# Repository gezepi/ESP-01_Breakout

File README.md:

# ESP-01_Breakout
A simple breakout board for an ESP-01 that has a protoboard area.  Provides 5v and 3v3 rails.

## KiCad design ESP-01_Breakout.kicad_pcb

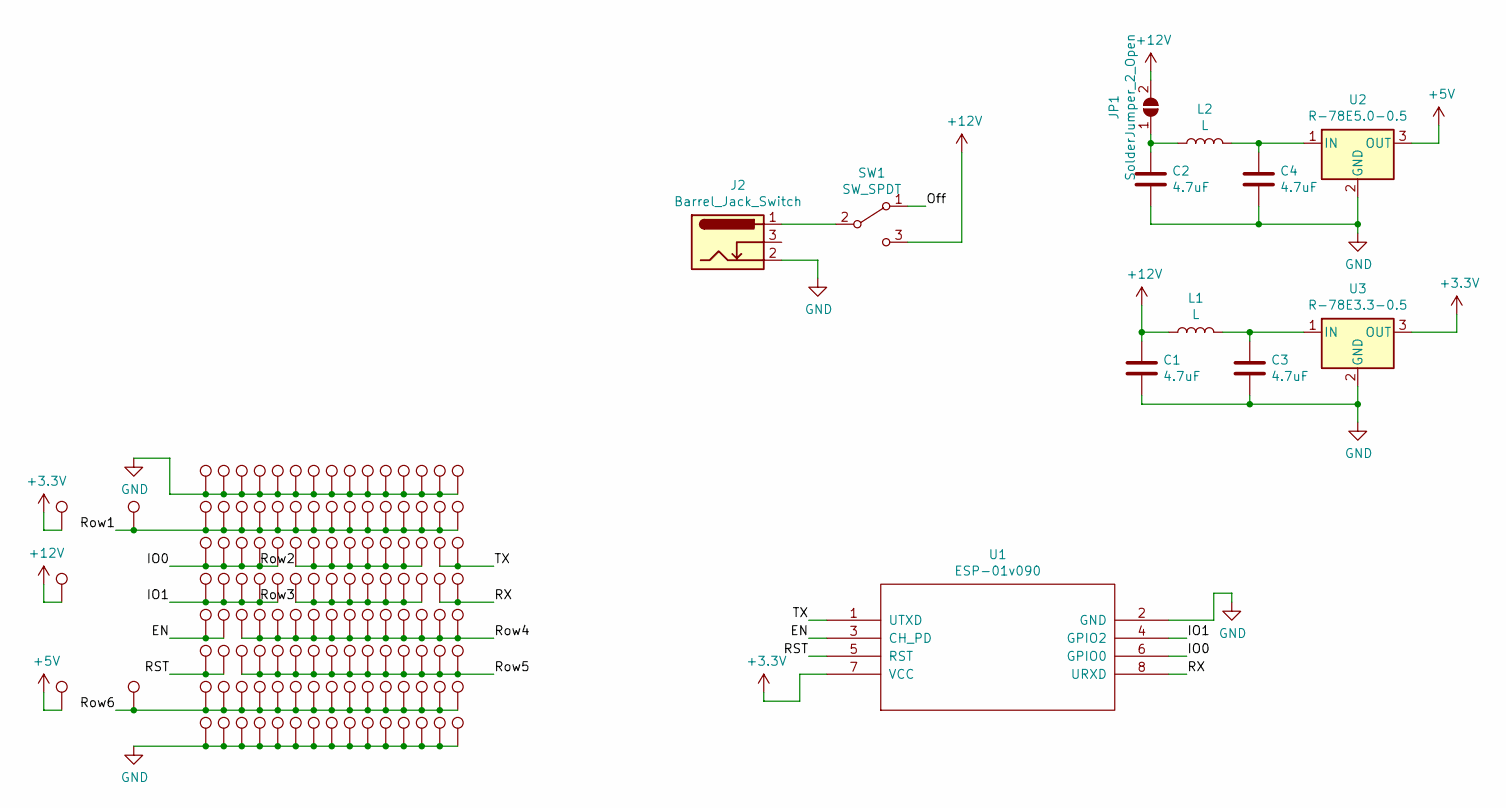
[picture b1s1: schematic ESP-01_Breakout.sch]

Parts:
C1, C2, C3, C4: 4.7uF; C_0805_2012Metric_Pad1.15x1.40mm_HandSolder; DigikeyPN 490-10751-1-ND
J2: Barrel_Jack_Switch; BarrelJack_Horizontal; DigikeyPN 2073-DCJ235-05-A-K1-K-ND
JP1: SolderJumper_2_Open; SolderJumper-2_P1.3mm_Open_TrianglePad1.0x1.5mm
L1, L2: L; IND_RLS-397; DigikeyPN 945-30004967-ND
SW1: SW_SPDT; SS312SAH4-R; DigikeyPN 360-2924-1-ND
TP1, TP2, TP3, TP4, TP5, TP6, TP7, TP8, TP9, TP10, TP11, TP12, TP13, TP14, TP15, TP16, TP17, TP18, TP19, TP20, TP21, TP22, TP23, TP24, TP25, TP26, TP27, TP28, TP29, TP30, TP31, TP32, TP33, TP34, TP35, TP36, TP37, TP38, TP39, TP40, TP41, TP42, TP43, TP44, TP45, TP46, TP47, TP48, TP49, TP50, TP51, TP52, TP53, TP54, TP55, TP56, TP57, TP58, TP59, TP60, TP61, TP62, TP63, TP64, TP65, TP66, TP67, TP68, TP69, TP70, TP71, TP72, TP73, TP74, TP75, TP76, TP77, TP78, TP79, TP80, TP81, TP82, TP83, TP84, TP85, TP86, TP87, TP88, TP89, TP90, TP91, TP92, TP93, TP94, TP95, TP96, TP97, TP98, TP99, TP100, TP101, TP102, TP103, TP104, TP105, TP106, TP107, TP108, TP109, TP110, TP111, TP112, TP113, TP114, TP115, TP116, TP117, TP118, TP119, TP120, TP121, TP122, TP123, TP124, TP125: TestPoint; TP
U1: ESP-01v090; ESP-01; DigikeyPN SAM1212-04-ND
U2: R-78E5.0-0.5; Converter_DCDC_RECOM_R-78E-0.5_THT; DigikeyPN 945-1648-5-ND
U3: R-78E3.3-0.5; Converter_DCDC_RECOM_R-78E-0.5_THT; DigikeyPN 945-1661-5-ND

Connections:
+3V3: TP121.1, U1.7 (VCC), U3.3 (OUT)
+5V: TP122.1, U2.3 (OUT)
+12V: C1.1, JP1.2 (B), L1.1, SW1.3 (C), TP125.1
/EN: TP109.1, TP117.1, U1.3 (CH_PD)
/IO0: TP3.1, TP11.1, TP19.1, TP27.1, TP35.1, U1.6 (GPIO0)
/IO1: TP4.1, TP12.1, TP20.1, TP28.1, TP36.1, U1.4 (GPIO2)
/Off: SW1.1 (A)
/RST: TP110.1, TP118.1, U1.5 (RST)
/RX: TP108.1, TP116.1, U1.8 (URXD)
/Row1: TP2.1, TP10.1, TP18.1, TP26.1, TP34.1, TP42.1, TP50.1, TP58.1, TP66.1, TP74.1, TP82.1, TP90.1, TP98.1, TP106.1, TP114.1, TP123.1
/Row2: TP43.1, TP51.1, TP59.1, TP67.1, TP75.1, TP83.1, TP91.1, TP99.1
/Row3: TP44.1, TP52.1, TP60.1, TP68.1, TP76.1, TP84.1, TP92.1, TP100.1
/Row4: TP5.1, TP13.1, TP21.1, TP29.1, TP37.1, TP45.1, TP53.1, TP61.1, TP69.1, TP77.1, TP85.1, TP93.1, TP101.1
/Row5: TP6.1, TP14.1, TP22.1, TP30.1, TP38.1, TP46.1, TP54.1, TP62.1, TP70.1, TP78.1, TP86.1, TP94.1, TP102.1
/Row6: TP7.1, TP15.1, TP23.1, TP31.1, TP39.1, TP47.1, TP55.1, TP63.1, TP71.1, TP79.1, TP87.1, TP95.1, TP103.1, TP111.1, TP119.1, TP124.1
/TX: TP107.1, TP115.1, U1.1 (UTXD)
GND: C1.2, C2.2, C3.2, C4.2, J2.2, TP1.1, TP8.1, TP9.1, TP16.1, TP17.1, TP24.1, TP25.1, TP32.1, TP33.1, TP40.1, TP41.1, TP48.1, TP49.1, TP56.1, TP57.1, TP64.1, TP65.1, TP72.1, TP73.1, TP80.1, TP81.1, TP88.1, TP89.1, TP96.1, TP97.1, TP104.1, TP105.1, TP112.1, TP113.1, TP120.1, U1.2 (GND), U2.2 (GND), U3.2 (GND)
unnamed: C2.1, JP1.1 (A), L2.1
unnamed: C3.1, L1.2, U3.1 (IN)
unnamed: C4.1, L2.2, U2.1 (IN)
unnamed: J2.1, SW1.2 (B)

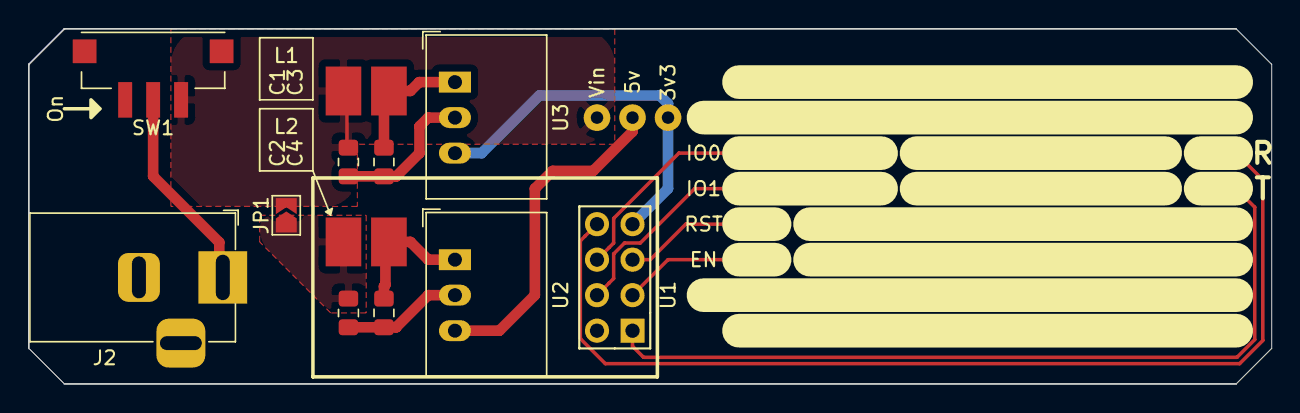
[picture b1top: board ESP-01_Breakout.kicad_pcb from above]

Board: 2 copper layers, 88.9 x 25.4 mm, 137 parts (0 on the bottom side), 20 nets.

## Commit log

2020-02-21 Initial Commit
    Has terminal block as power input
2020-02-21 Barrel Jack, Smaller Switch
2020-02-21 BOM, gitignore Update
2020-02-21 Add Release Action
    See here: https://github.com/actions/create-release
2020-02-21 Revert "Add Release Action"
    This reverts commit 27405666da6dad12f90c6b98284779e225da4cfb.
2020-02-21 Update BOM Info
2020-02-21 Add Inductor 3D Model
2020-02-29 Updated Footprints, Added 5v Solder Jumper
    Slight tweak to silkscreen tezt
